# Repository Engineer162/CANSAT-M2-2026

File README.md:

# CANSAT-M2-2026 "Rod From God MK1"

This repository contains all the sources for a highly advanced CANSAT based on an STM32 MCU and featuring a rechargeable lithium polymer battery.

Core hardware fields:

| Component        | Model           | Manufacturer       |
| ---------------- | --------------- | ------------------ |
| STM32 MCU (core) | STM32H7S3L8H6   | STMicroelectronics |

Power system:

| Component          | Model                   | Manufacturer       |
| ------------------ | ----------------------- | ------------------ |
| STM32 MCU (power)  | STM32L031G6U6           | STMicroelectronics |
| USB-C Connector    | 12402012E212A           | Amphenol           |
| Battery Management | BQ25895RTWT             | Texas Instruments  |
| PD Negotiation     | TPS25730DREFR           | Texas Instruments  |
| Battery            | 1260110 (10000mAh LiPo) | TBD                |

Additionally, it features numerous different sensors for logging, as listed below:

| Sensor                | Model          | Manufacturer       |
| --------------------- | -------------- | ------------------ |
| IMU                   | ICM-42688-PC   | Tokmas             |
| Barometer             | BMP581         | BOSCH              |
| Magnetometer          | MMC5983MA      | MEMSIC             |
| Temperature (outside) | TMP121AIDBVR   | Texas Instruments  |
| Temperature (inside)  | TMP121AIDBVR   | Texas Instruments  |
| Ground distance (ToF) | VL53L1CXV0FY/1 | STMicroelectronics |

And debugging/programming is done via a TAG-CONNECT TC2050-IDC "Plug-Of-Nails™" connector.

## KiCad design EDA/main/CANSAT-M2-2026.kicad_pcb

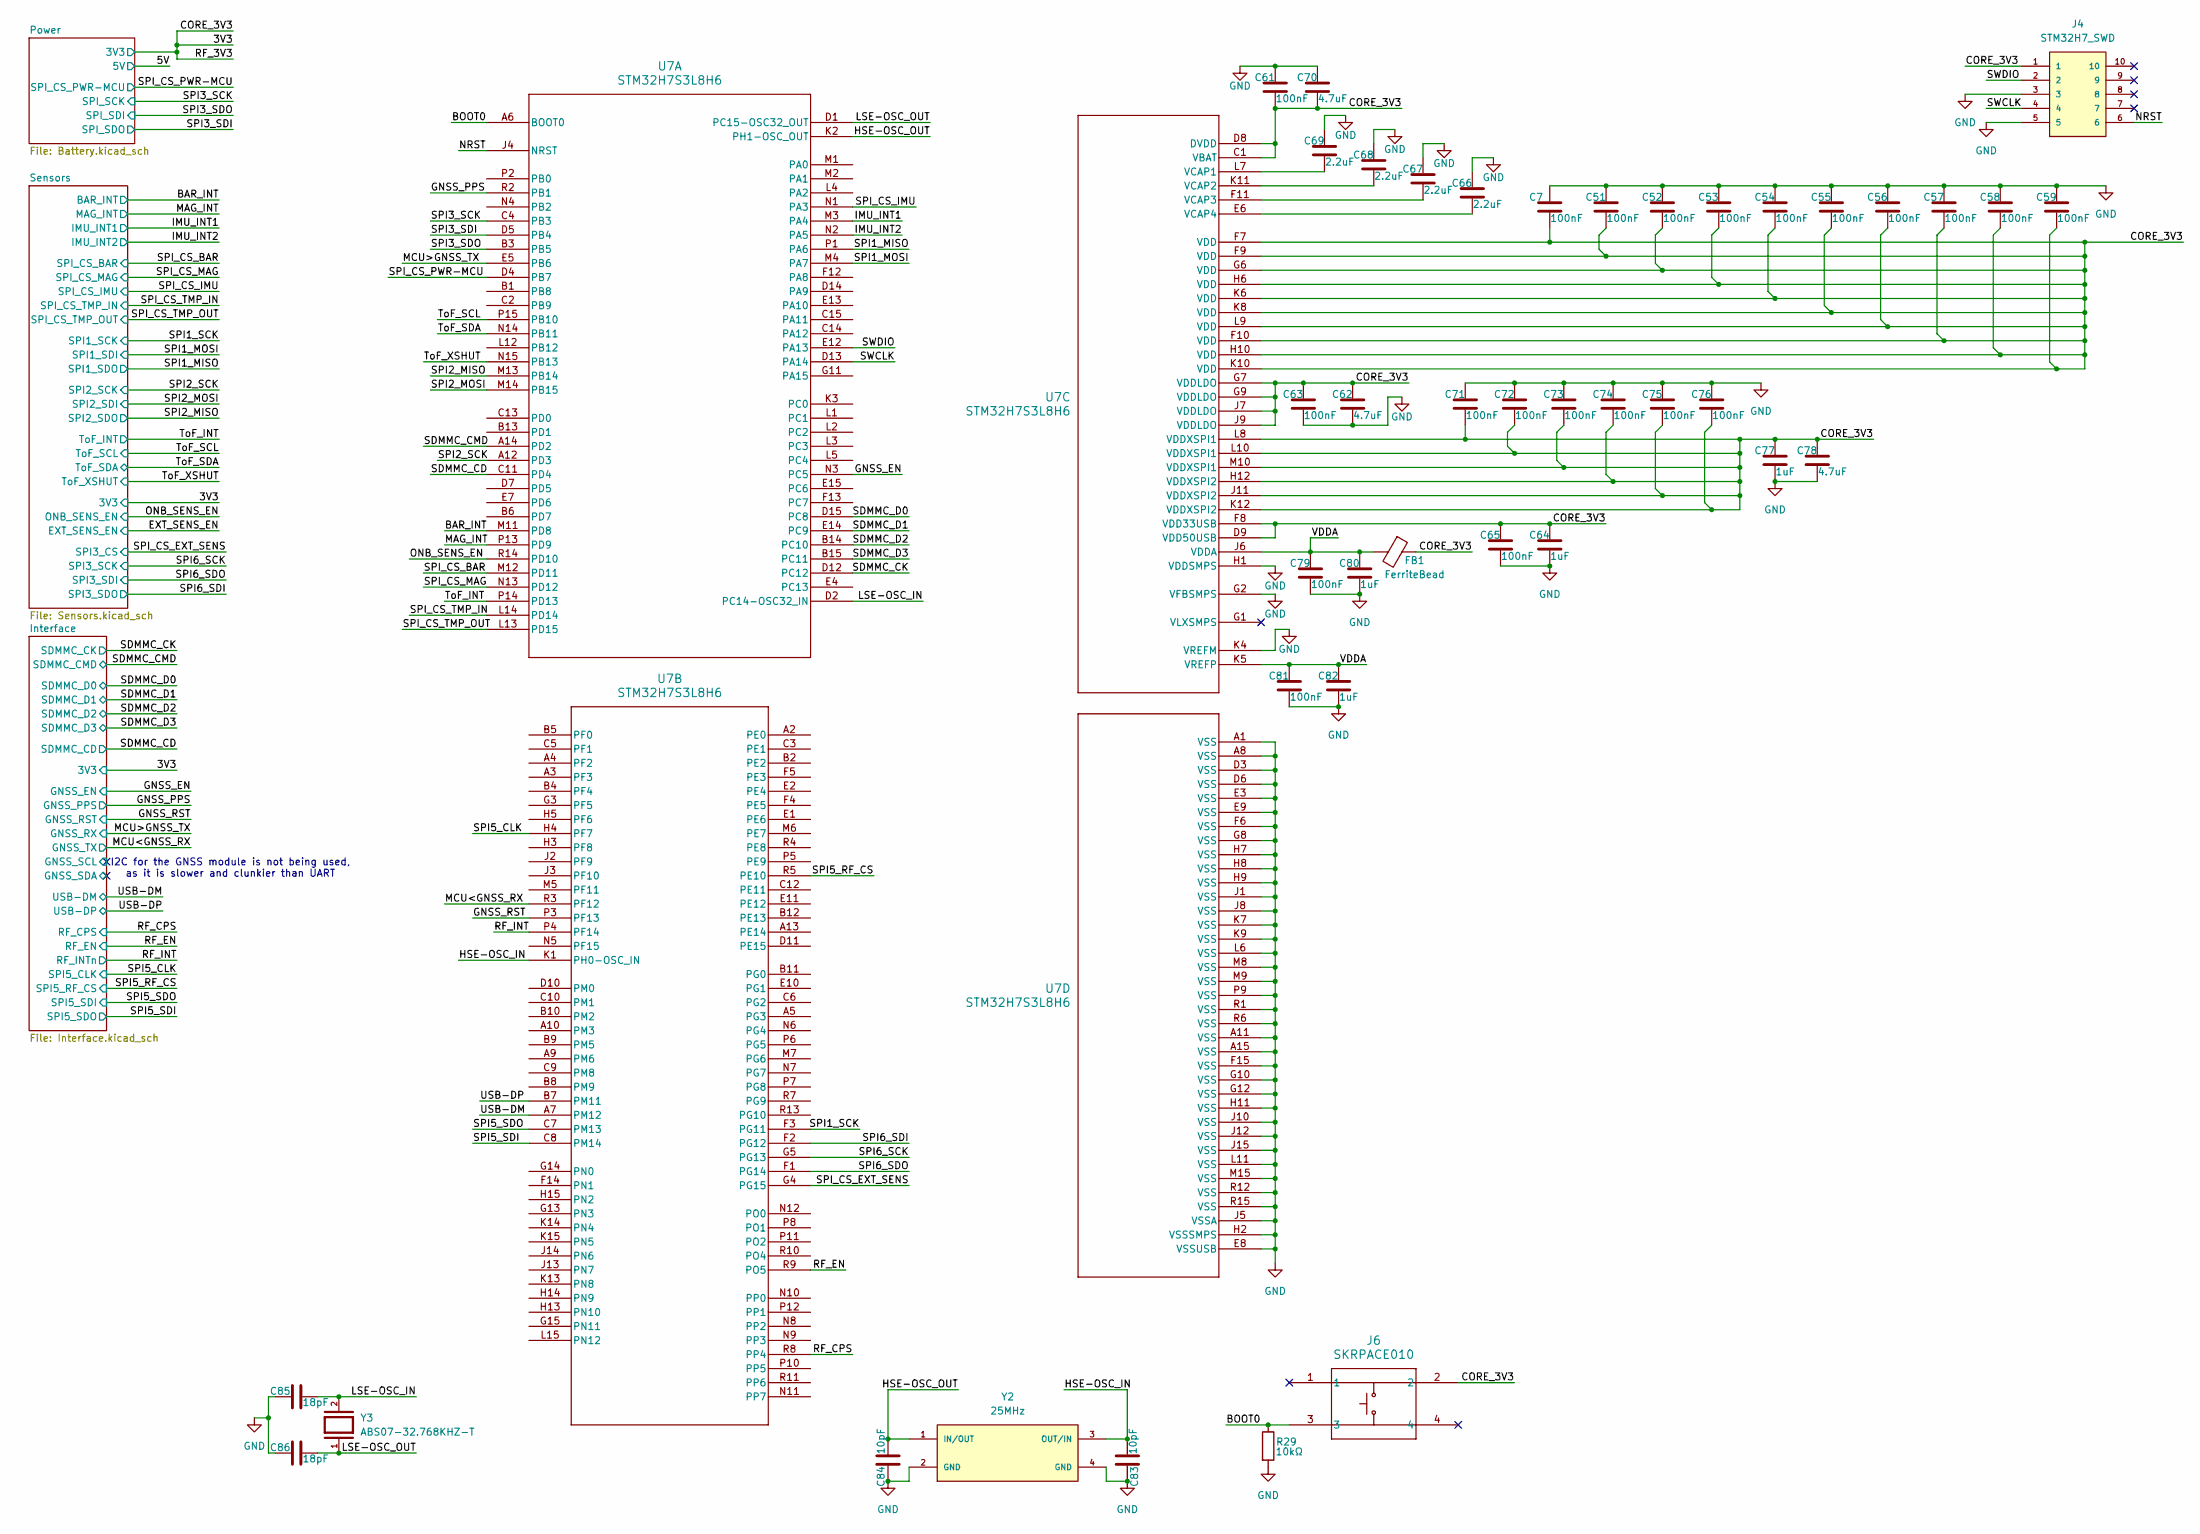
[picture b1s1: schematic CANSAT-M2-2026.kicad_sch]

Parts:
C7, C51, C52, C53, C54, C55, C56, C57, C58, C59, C61, C63, C65, C71, C72, C73, C74, C75, C76, C79, C81: 100nF; C_0402_1005Metric; Manufacturer Part CL05B104KP5NNNC
C62, C70, C78: 4.7uF; C_0603_1608Metric; Manufacturer Part CL10A475KP8NNNC
C64, C77, C80, C82: 1uF; C_0603_1608Metric; Manufacturer Part CL10B105MO8NNWC
C66, C67, C68, C69: 2.2uF; C_0603_1608Metric; Manufacturer Part CL10A225KO8NNNC
C83, C84: 10pF; C_0402_1005Metric; Manufacturer Part CL05C100JB5NNNC
C85, C86: 18pF; C_0402_1005Metric; Manufacturer Part CL05C180JB5NNNC
FB1: FerriteBead; L_0603_1608Metric; Manufacturer Part MMZ1608D121CTAH0
J4: STM32H7_SWD; TAG-CONNECT_TC2050-IDC; PARTREV A; DigiKey_Part_Number TC2050-IDC-ND
J6: SKRPACE010; SW_SKRPACE010_AAL; Manufacturer Part SKRPACE010
R29: 10kΩ; R_0402_1005Metric; Manufacturer Part RC0402FR-0710KL
U7: STM32H7S3L8H6; TFBGA225_13X13_STM; Manufacturer Part STM32H7S3L8H6H
Y2: 25MHz; XTAL_ECS-160-9-37-CKM-TR; PARTREV 2017
Y3: ABS07-32.768KHZ-T; XTAL_ABS07-32.768KHZ-T; PARTREV 08.19.15; DigiKey_Part_Number 535-9542-1-ND

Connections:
/3V3: C7.2, C51.2, C52.2, C53.2, C54.2, C55.2, C56.2, C57.2, C58.2, C59.2, C61.2, C62.1, C63.1, C64.1, C65.1, C70.2, C71.2, C72.2, C73.2, C74.2, C75.2, C76.2, C77.1, C78.1, FB1.1, J4.1, J6.2, U7.C1 (VBAT), U7.D8 (DVDD), U7.D9 (VDD50USB), U7.F7 (VDD), U7.F8 (VDD33USB), U7.F9 (VDD), U7.F10 (VDD), U7.G6 (VDD), U7.G7 (VDDLDO), U7.G9 (VDDLDO), U7.H6 (VDD), U7.H10 (VDD), U7.H12 (VDDXSPI2), U7.J7 (VDDLDO), U7.J9 (VDDLDO), U7.J11 (VDDXSPI2), U7.K6 (VDD), U7.K8 (VDD), U7.K10 (VDD), U7.K12 (VDDXSPI2), U7.L8 (VDDXSPI1), U7.L9 (VDD), U7.L10 (VDDXSPI1), U7.M10 (VDDXSPI1); also elsewhere on the board
/BAR_INT: U7.M11 (PD8); also elsewhere on the board
/BOOT0: J6.3, R29.1, U7.A6 (BOOT0)
/GNSS_EN: U7.N3 (PC5); also elsewhere on the board
/GNSS_PPS: U7.R2 (PB1); also elsewhere on the board
/GNSS_RST: U7.P3 (PF13); also elsewhere on the board
/HSE-OSC_IN: C83.2, U7.K1 (PH0-OSC_IN), Y2.3 (OUT/IN)
/HSE-OSC_OUT: C84.2, U7.K2 (PH1-OSC_OUT), Y2.1 (IN/OUT)
/IMU_INT1: U7.M3 (PA4); also elsewhere on the board
/IMU_INT2: U7.N2 (PA5); also elsewhere on the board
/LSE-OSC_IN: C85.2, U7.D2 (PC14-OSC32_IN), Y3.2
/LSE-OSC_OUT: C86.2, U7.D1 (PC15-OSC32_OUT), Y3.1
/MAG_INT: U7.P13 (PD9); also elsewhere on the board
/MCU<GNSS_RX: U7.R3 (PF12); also elsewhere on the board
/MCU>GNSS_TX: U7.E5 (PB6); also elsewhere on the board
/NRST: J4.6, U7.J4 (NRST)
/ONB_SENS_EN: U7.R14 (PD10); also elsewhere on the board
/RF_CPS: U7.R8 (PP4); also elsewhere on the board
/RF_EN: U7.R9 (PO5); also elsewhere on the board
/RF_INT: U7.P4 (PF14); also elsewhere on the board
/SDMMC_CD: U7.C11 (PD4); also elsewhere on the board
/SDMMC_CK: U7.D12 (PC12); also elsewhere on the board
/SDMMC_CMD: U7.A14 (PD2); also elsewhere on the board
/SDMMC_D0: U7.D15 (PC8); also elsewhere on the board
/SDMMC_D1: U7.E14 (PC9); also elsewhere on the board
/SDMMC_D2: U7.B14 (PC10); also elsewhere on the board
/SDMMC_D3: U7.B15 (PC11); also elsewhere on the board
/SPI1_MISO: U7.P1 (PA6); also elsewhere on the board
/SPI1_MOSI: U7.M4 (PA7); also elsewhere on the board
/SPI1_SCK: U7.F3 (PG11); also elsewhere on the board
/SPI2_MISO: U7.M13 (PB14); also elsewhere on the board
/SPI2_MOSI: U7.M14 (PB15); also elsewhere on the board
/SPI2_SCK: U7.A12 (PD3); also elsewhere on the board
/SPI3_SCK: U7.C4 (PB3); also elsewhere on the board
/SPI3_SDI: U7.D5 (PB4); also elsewhere on the board
/SPI3_SDO: U7.B3 (PB5); also elsewhere on the board
/SPI5_CLK: U7.H4 (PF7); also elsewhere on the board
/SPI5_RF_CS: U7.R5 (PE10); also elsewhere on the board
/SPI5_SDI: U7.C8 (PM14); also elsewhere on the board
/SPI5_SDO: U7.C7 (PM13); also elsewhere on the board
/SPI6_SCK: U7.G5 (PG13); also elsewhere on the board
/SPI6_SDI: U7.F2 (PG12); also elsewhere on the board
/SPI6_SDO: U7.F1 (PG14); also elsewhere on the board
/SPI_CS_BAR: U7.M12 (PD11); also elsewhere on the board
/SPI_CS_EXT_SENS: U7.G4 (PG15); also elsewhere on the board
/SPI_CS_IMU: U7.N1 (PA3); also elsewhere on the board
/SPI_CS_MAG: U7.N13 (PD12); also elsewhere on the board
/SPI_CS_PWR-MCU: U7.D4 (PB7); also elsewhere on the board
/SPI_CS_TMP_IN: U7.L14 (PD14); also elsewhere on the board
/SPI_CS_TMP_OUT: U7.L13 (PD15); also elsewhere on the board
/SWCLK: J4.4, U7.D13 (PA14)
/SWDIO: J4.2, U7.E12 (PA13)
/ToF_INT: U7.P14 (PD13); also elsewhere on the board
/ToF_SCL: U7.P15 (PB10); also elsewhere on the board
/ToF_SDA: U7.N14 (PB11); also elsewhere on the board
/ToF_XSHUT: U7.N15 (PB13); also elsewhere on the board
/USB-DM: U7.A7 (PM12); also elsewhere on the board
/USB-DP: U7.B7 (PM11); also elsewhere on the board
/VDDA: C79.1, C80.1, C81.1, C82.1, FB1.2, U7.J6 (VDDA), U7.K5 (VREFP)
GND: C7.1, C51.1, C52.1, C53.1, C54.1, C55.1, C56.1, C57.1, C58.1, C59.1, C61.1, C62.2, C63.2, C64.2, C65.2, C66.1, C67.1, C68.1, C69.1, C70.1, C71.1, C72.1, C73.1, C74.1, C75.1, C76.1, C77.2, C78.2, C79.2, C80.2, C81.2, C82.2, C83.1, C84.1, C85.1, C86.1, J4.3, J4.5, R29.2, U7.A1 (VSS), U7.A8 (VSS), U7.A11 (VSS), U7.A15 (VSS), U7.D3 (VSS), U7.D6 (VSS), U7.E3 (VSS), U7.E8 (VSSUSB), U7.E9 (VSS), U7.F6 (VSS), U7.F15 (VSS), U7.G2 (VFBSMPS), U7.G8 (VSS), U7.G10 (VSS), U7.G12 (VSS), U7.H1 (VDDSMPS), U7.H2 (VSSSMPS), U7.H7 (VSS), U7.H8 (VSS), U7.H9 (VSS), U7.H11 (VSS), U7.J1 (VSS), U7.J5 (VSSA), U7.J8 (VSS), U7.J10 (VSS), U7.J12 (VSS), U7.J15 (VSS), U7.K4 (VREFM), U7.K7 (VSS), U7.K9 (VSS), U7.L6 (VSS), U7.L11 (VSS), U7.M8 (VSS), U7.M9 (VSS), U7.M15 (VSS), U7.P9 (VSS), U7.R1 (VSS), U7.R6 (VSS), U7.R12 (VSS), U7.R15 (VSS), Y2.2 (GND), Y2.4 (GND); also elsewhere on the board
unnamed: C69.2, U7.L7 (VCAP1)
unnamed: C68.2, U7.K11 (VCAP2)
unnamed: C67.2, U7.F11 (VCAP3)
unnamed: C66.2, U7.E6 (VCAP4)

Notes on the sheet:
I2C for the GNSS module is not being used, as it is slower and clunkier than UART

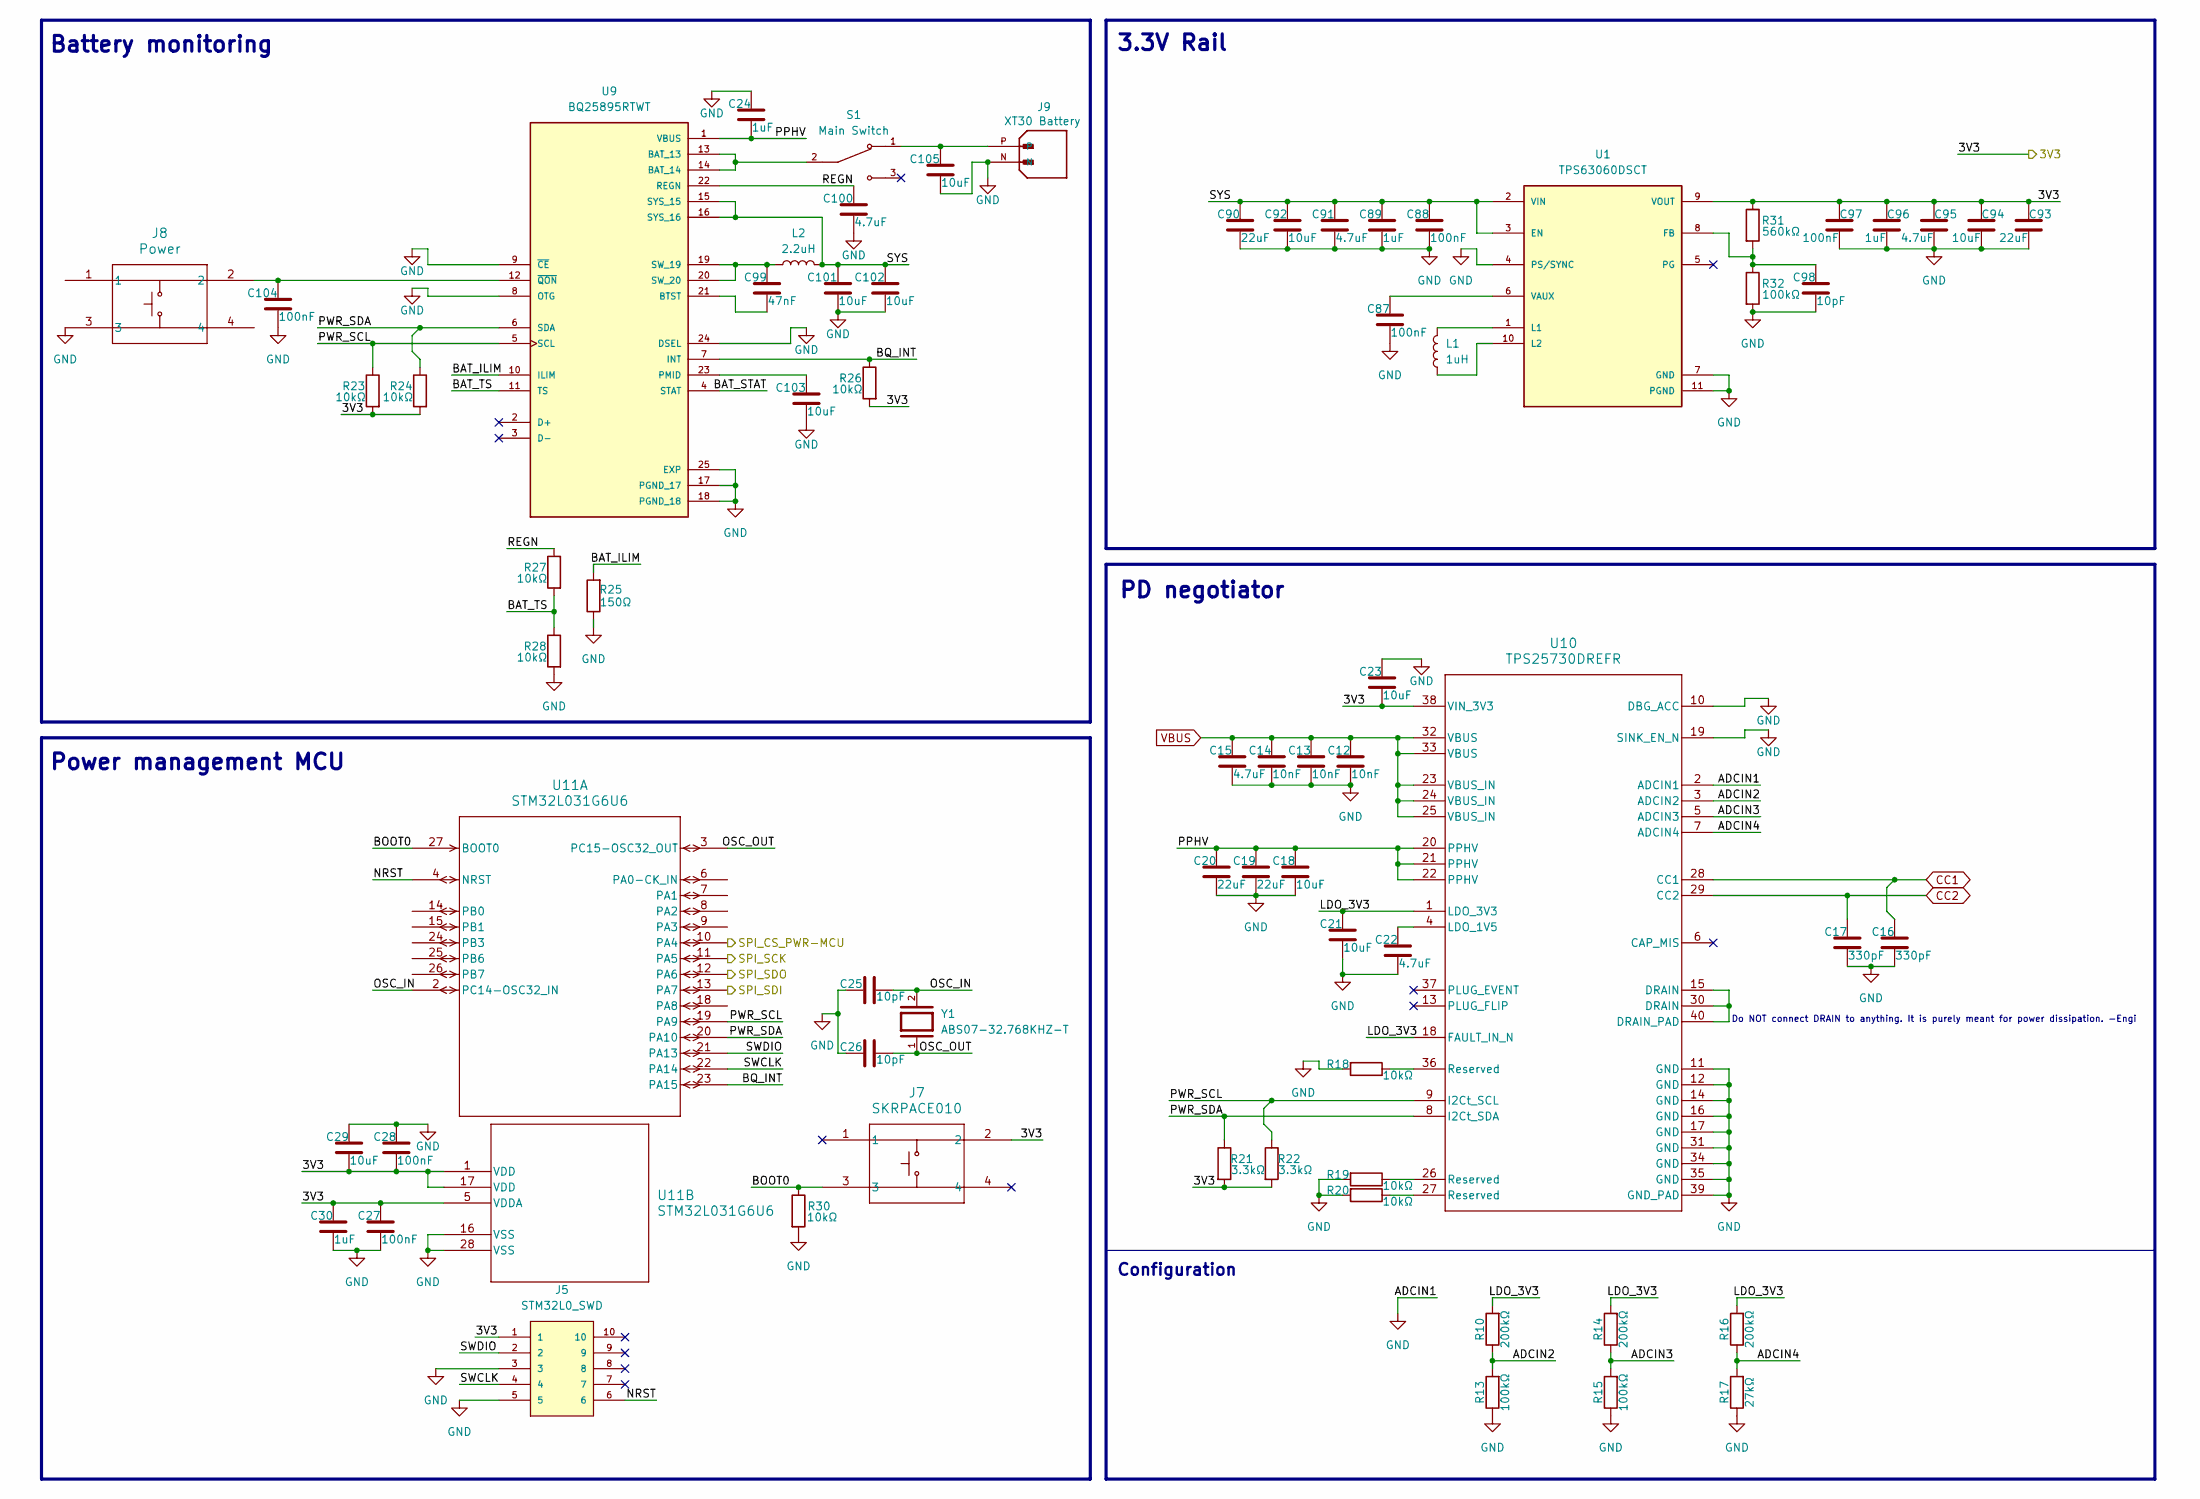
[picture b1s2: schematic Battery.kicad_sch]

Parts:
C12, C13, C14: 10nF; C_0402_1005Metric; Manufacturer Part CL05B103KB5NNNC
C15, C22, C91, C95, C100: 4.7uF; C_0603_1608Metric; Manufacturer Part CL10A475KP8NNNC
C16, C17: 330pF; C_0402_1005Metric; Manufacturer Part CL05C331JB5NNNC
C18, C21, C23, C29, C92, C94, C101, C102, C103, C105: 10uF; C_0603_1608Metric; Manufacturer Part CL10X106MO8NRNC
C19, C20, C90, C93: 22uF; C_0603_1608Metric; Manufacturer Part CL10A226MP8NUNE
C24, C30, C89, C96: 1uF; C_0603_1608Metric; Manufacturer Part CL10B105MO8NNWC
C25, C26, C98: 10pF; C_0402_1005Metric; Manufacturer Part CL05C100JB5NNNC
C27, C28, C87, C88, C97, C104: 100nF; C_0402_1005Metric; Manufacturer Part CL05B104KP5NNNC
C99: 47nF; C_0402_1005Metric; Manufacturer Part CL05B473KB5VPNC
J5: STM32L0_SWD; TAG-CONNECT_TC2050-IDC; PARTREV A; DigiKey_Part_Number TC2050-IDC-ND
J7: SKRPACE010; SW_SKRPACE010_AAL; Manufacturer Part SKRPACE010
J8: Power; SW_SKRPACE010_AAL; Manufacturer Part SKRPACE010
J9: XT30 Battery; AMASS_XT30PW-M; PARTREV 1.2
L1: 1uH; L_1008_2520Metric; Manufacturer Part 74438324010
L2: 2.2uH; L_Wuerth_MAPI-4020; Manufacturer Part 74438356022
R10, R14, R16: 200kΩ; R_0603_1608Metric; Manufacturer Part RC0603JR-07200KL
R13, R15: 100kΩ; R_0603_1608Metric; Manufacturer Part RC0603FR-07100KL
R17: 27kΩ; R_0603_1608Metric; Manufacturer Part RC0603FR-1027KL
R18, R19, R20, R23, R24, R26, R27, R28, R30: 10kΩ; R_0402_1005Metric; Manufacturer Part RC0402FR-0710KL
R21, R22: 3.3kΩ; R_0402_1005Metric; Manufacturer Part RC0402FR-073K3L
R25: 150Ω; R_0603_1608Metric; Manufacturer Part RC0603FR-07150RL
R31: 560kΩ; R_0402_1005Metric; Manufacturer Part RC0402FR-13560KL
R32: 100kΩ; R_0402_1005Metric; Manufacturer Part RC0402FR-07100KL
S1: Main Switch; SW_500SSP1S1M6QEA; PARTREV D
U1: TPS63060DSCT; CONV_TPS63060DSCT; PARTREV B
U9: BQ25895RTWT; QFN50P400X400X80-25N; PARTREV B
U10: TPS25730DREFR; REF0038A-MFG; Manufacturer Part TPS25730DREFR
U11: STM32L031G6U6; UFQFPN28-4x4mm; Manufacturer Part STM32L031G6U6
Y1: ABS07-32.768KHZ-T; XTAL_ABS07-32.768KHZ-T; PARTREV 08.19.15; DigiKey_Part_Number 535-9542-1-ND

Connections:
/3V3: C23.2, C27.1, C28.2, C29.2, C30.1, C93.1, C94.1, C95.1, C96.1, C97.1, J5.1, J7.2, R21.2, R22.2, R23.2, R24.2, R26.2, R31.1, U1.9 (VOUT), U10.38 (VIN_3V3), U11.1 (VDD), U11.5 (VDDA), U11.17 (VDD); also elsewhere on the board
/Power/ADCIN2: R10.1, R13.2, U10.3 (ADCIN2)
/Power/ADCIN3: R14.1, R15.2, U10.5 (ADCIN3)
/Power/ADCIN4: R16.1, R17.2, U10.7 (ADCIN4)
/Power/BAT_ILIM: R25.2, U9.10 (ILIM)
/Power/BAT_STAT: U9.4 (STAT)
/Power/BAT_TS: R27.2, R28.1, U9.11 (TS)
/Power/BOOT0: J7.3, R30.1, U11.27 (BOOT0)
/Power/BQ_INT: R26.1, U9.7 (INT), U11.23 (PA15)
/Power/LDO_3V3: C21.1, R10.2, R14.2, R16.2, U10.1 (LDO_3V3), U10.18 (FAULT_IN_N)
/Power/NRST: J5.6, U11.4 (NRST)
/Power/OSC_IN: C25.2, U11.2 (PC14-OSC32_IN), Y1.2
/Power/OSC_OUT: C26.2, U11.3 (PC15-OSC32_OUT), Y1.1
/Power/PPHV: C18.1, C19.1, C20.1, C24.2, U9.1 (VBUS), U10.20 (PPHV), U10.21 (PPHV), U10.22 (PPHV)
/Power/PWR_SCL: R22.1, R23.1, U9.5 (SCL), U10.9 (I2Ct_SCL), U11.19 (PA9)
/Power/PWR_SDA: R21.1, R24.1, U9.6 (SDA), U10.8 (I2Ct_SDA), U11.20 (PA10)
/Power/REGN: C100.1, R27.1, U9.22 (REGN)
/Power/SWCLK: J5.4, U11.22 (PA14)
/Power/SWDIO: J5.2, U11.21 (PA13)
/Power/SYS: C88.1, C89.1, C90.1, C91.1, C92.1, C101.1, C102.1, L2.2, U1.2 (VIN), U1.3 (EN), U9.15 (SYS_15), U9.16 (SYS_16)
/SPI3_SCK: U11.11 (PA5); also elsewhere on the board
/SPI3_SDI: U11.12 (PA6); also elsewhere on the board
/SPI3_SDO: U11.13 (PA7); also elsewhere on the board
/SPI_CS_PWR-MCU: U11.10 (PA4); also elsewhere on the board
CC1: C16.1, U10.28 (CC1); also elsewhere on the board
CC2: C17.1, U10.29 (CC2); also elsewhere on the board
GND: C12.2, C13.2, C14.2, C15.2, C16.2, C17.2, C18.2, C19.2, C20.2, C21.2, C22.2, C23.1, C24.1, C25.1, C26.1, C27.2, C28.1, C29.1, C30.2, C87.2, C88.2, C89.2, C90.2, C91.2, C92.2, C93.2, C94.2, C95.2, C96.2, C97.2, C98.2, C100.2, C101.2, C102.2, C103.2, C104.2, C105.2, J5.3, J5.5, J8.3, J9.N, R13.1, R15.1, R17.1, R18.2, R19.2, R20.2, R25.1, R28.2, R30.2, R32.2, U1.4 (PS/SYNC), U1.7 (GND), U1.11 (PGND), U9.8 (OTG), U9.9 (~CE), U9.17 (PGND_17), U9.18 (PGND_18), U9.24 (DSEL), U9.25 (EXP), U10.2 (ADCIN1), U10.10 (DBG_ACC), U10.11 (GND), U10.12 (GND), U10.14 (GND), U10.16 (GND), U10.17 (GND), U10.19 (SINK_EN_N), U10.31 (GND), U10.34 (GND), U10.35 (GND), U10.39 (GND_PAD), U11.16 (VSS), U11.28 (VSS); also elsewhere on the board
unnamed: C105.1, J9.P, S1.1
unnamed: R18.1, U10.36 (Reserved)
unnamed: R19.1, U10.26 (Reserved)
unnamed: R20.1, U10.27 (Reserved)
unnamed: C98.1, R31.2, R32.1, U1.8 (FB)
unnamed: L1.2, U1.1 (L1)
unnamed: L1.1, U1.10 (L2)
unnamed: C87.1, U1.6 (VAUX)
unnamed: S1.2, U9.13 (BAT_13), U9.14 (BAT_14)
unnamed: C99.2, U9.21 (BTST)
unnamed: C103.1, U9.23 (PMID)
unnamed: C99.1, L2.1, U9.19 (SW_19), U9.20 (SW_20)
unnamed: C104.1, J8.2, U9.12 (~QON)
unnamed: U10.15 (DRAIN), U10.30 (DRAIN), U10.40 (DRAIN_PAD)
unnamed: C22.1, U10.4 (LDO_1V5)
VBUS: C12.1, C13.1, C14.1, C15.1, U10.23 (VBUS_IN), U10.24 (VBUS_IN), U10.25 (VBUS_IN), U10.32 (VBUS), U10.33 (VBUS); also elsewhere on the board

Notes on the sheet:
Power management MCU
Battery monitoring
3.3V Rail
Configuration
Do NOT connect DRAIN to anything. It is purely meant for power dissipation. -Engi
PD negotiator

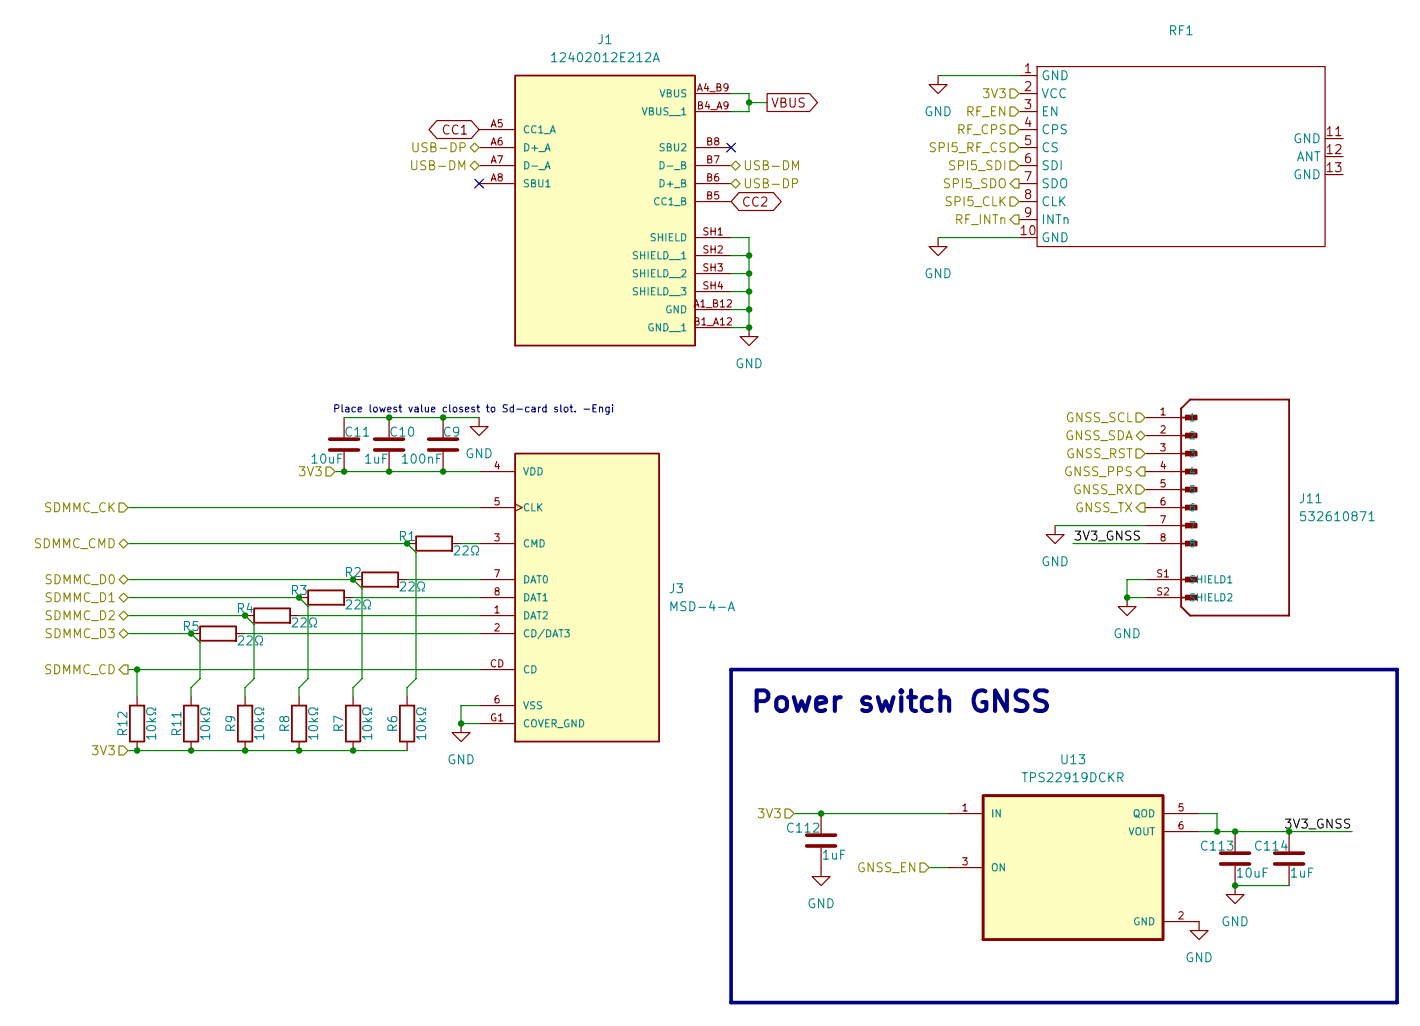
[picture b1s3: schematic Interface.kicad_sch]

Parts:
C9: 100nF; C_0402_1005Metric; Manufacturer Part CL05B104KP5NNNC
C10, C112, C114: 1uF; C_0603_1608Metric; Manufacturer Part CL10B105MO8NNWC
C11, C113: 10uF; C_0603_1608Metric; Manufacturer Part CL10X106MO8NRNC
J1: 12402012E212A; AMPHENOL_USB-C_12402012E212A; PARTREV 4
J3: MSD-4-A; CUI_MSD-4-A; PARTREV 1.0; DigiKey_Part_Number 2223-MSD-4-ACT-ND
J11: 532610871; MOLEX_532610871; PARTREV J
R1, R2, R3, R4, R5: 22Ω; R_0402_1005Metric; Manufacturer Part RC0402FR-0722RL
R6, R7, R8, R9, R11, R12: 10kΩ; R_0402_1005Metric; Manufacturer Part RC0402FR-0710KL
RF1: SI4463-MODULE
U13: TPS22919DCKR; SOT65P210X110-6N; Manufacturer Part TPS22919DCKR

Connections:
/3V3: C9.2, C10.2, C11.2, C112.1, J3.4 (VDD), R6.1, R7.1, R8.1, R9.1, R11.1, R12.1, RF1.2 (VCC), U13.1 (IN); also elsewhere on the board
/GNSS_EN: U13.3 (ON); also elsewhere on the board
/GNSS_PPS: J11.4; also elsewhere on the board
/GNSS_RST: J11.3; also elsewhere on the board
/Interface/3V3_GNSS: C113.1, C114.1, J11.8, U13.5 (QOD), U13.6 (VOUT)
/Interface/GNSS_SCL: J11.1
/Interface/GNSS_SDA: J11.2
/MCU<GNSS_RX: J11.6; also elsewhere on the board
/MCU>GNSS_TX: J11.5; also elsewhere on the board
/RF_CPS: RF1.4 (CPS); also elsewhere on the board
/RF_EN: RF1.3 (EN); also elsewhere on the board
/RF_INT: RF1.9 (INTn); also elsewhere on the board
/SDMMC_CD: J3.CD, R12.2; also elsewhere on the board
/SDMMC_CK: J3.5 (CLK); also elsewhere on the board
/SDMMC_CMD: R1.1, R6.2; also elsewhere on the board
/SDMMC_D0: R2.1, R7.2; also elsewhere on the board
/SDMMC_D1: R3.1, R8.2; also elsewhere on the board
/SDMMC_D2: R4.1, R9.2; also elsewhere on the board
/SDMMC_D3: R5.1, R11.2; also elsewhere on the board
/SPI5_CLK: RF1.8 (CLK); also elsewhere on the board
/SPI5_RF_CS: RF1.5 (CS); also elsewhere on the board
/SPI5_SDI: RF1.7 (SDO); also elsewhere on the board
/SPI5_SDO: RF1.6 (SDI); also elsewhere on the board
/USB-DM: J1.A7 (D-_A), J1.B7 (D-_B); also elsewhere on the board
/USB-DP: J1.A6 (D+_A), J1.B6 (D+_B); also elsewhere on the board
CC1: J1.A5 (CC1_A); also elsewhere on the board
CC2: J1.B5 (CC1_B); also elsewhere on the board
GND: C9.1, C10.1, C11.1, C112.2, C113.2, C114.2, J1.A1_B12 (GND), J1.B1_A12 (GND__1), J1.SH1 (SHIELD), J1.SH2 (SHIELD__1), J1.SH3 (SHIELD__2), J1.SH4 (SHIELD__3), J3.6 (VSS), J3.G1 (COVER_GND), J3.G2 (COVER_GND), J3.G3 (COVER_GND), J3.G4 (COVER_GND), J11.7, J11.S1 (SHIELD1), J11.S2 (SHIELD2), RF1.1 (GND), RF1.10 (GND), U13.2 (GND); also elsewhere on the board
unnamed: J3.2 (CD/DAT3), R5.2
unnamed: J3.3 (CMD), R1.2
unnamed: J3.7 (DAT0), R2.2
unnamed: J3.8 (DAT1), R3.2
unnamed: J3.1 (DAT2), R4.2
VBUS: J1.A4_B9 (VBUS), J1.B4_A9 (VBUS__1); also elsewhere on the board

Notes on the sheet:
Place lowest value closest to Sd-card slot. -Engi
Power switch GNSS

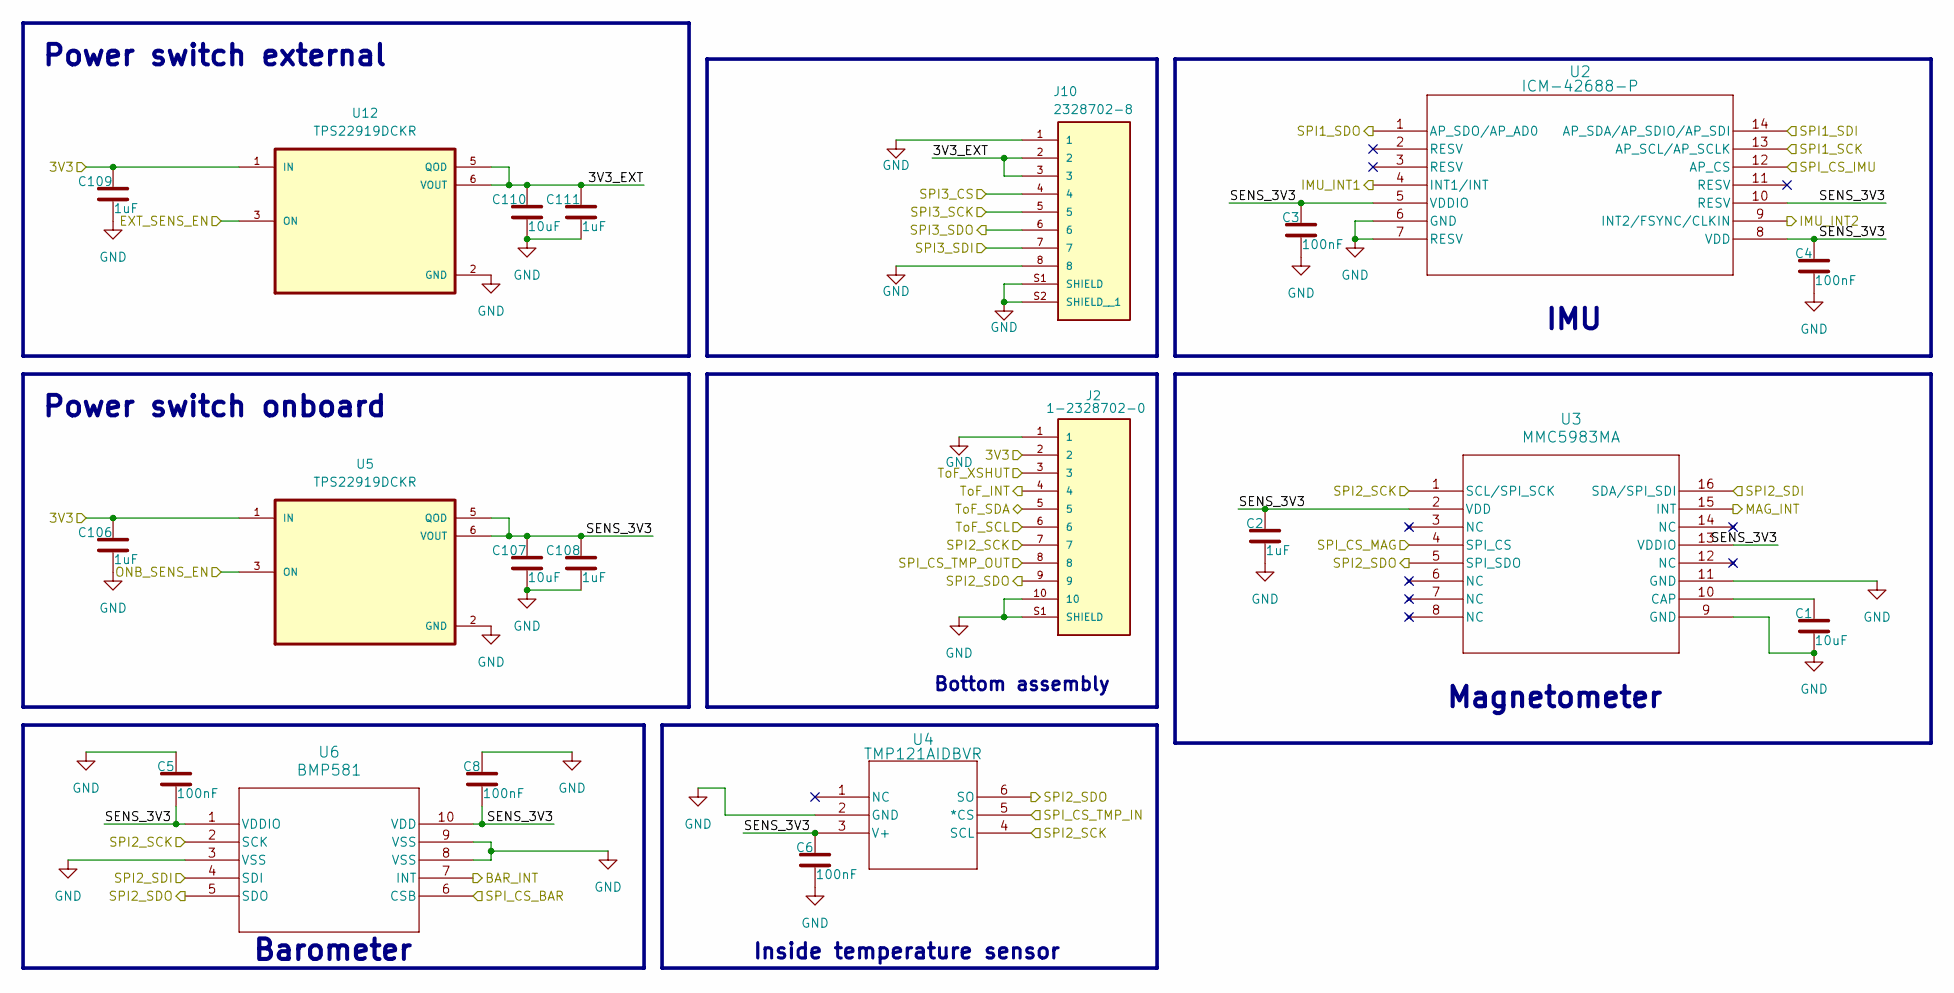
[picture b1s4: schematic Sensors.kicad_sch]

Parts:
C1, C107, C110: 10uF; C_0603_1608Metric; Manufacturer Part CL10X106MO8NRNC
C2, C106, C108, C109, C111: 1uF; C_0603_1608Metric; Manufacturer Part CL10B105MO8NNWC
C3, C4, C5, C6, C8: 100nF; C_0402_1005Metric; Manufacturer Part CL05B104KP5NNNC
J2: 1-2328702-0; TE_1-2328702-0; PARTREV 5; DigiKey_Part_Number A141390CT-ND
J10: 2328702-8; TE_2328702-8; PARTREV 5
U2: ICM-42688-P; LGA14_2P5X3X0P91_TDK; Manufacturer Part ICM-42688-P
U3: MMC5983MA; MMC5983MA_MEM; Manufacturer Part MMC5983MA
U4: TMP121AIDBVR; DBV6; Manufacturer Part TMP121AIDBVR
U5, U12: TPS22919DCKR; SOT65P210X110-6N; Manufacturer Part TPS22919DCKR
U6: BMP581; QFN10_BMP581_BOS; Manufacturer Part BMP581

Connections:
/3V3: C106.1, C109.1, J2.2, U5.1 (IN), U12.1 (IN); also elsewhere on the board
/BAR_INT: U6.7 (INT); also elsewhere on the board
/EXT_SENS_EN: U12.3 (ON)
/IMU_INT1: U2.4 (INT1/INT); also elsewhere on the board
/IMU_INT2: U2.9 (INT2/FSYNC/CLKIN); also elsewhere on the board
/MAG_INT: U3.15 (INT); also elsewhere on the board
/ONB_SENS_EN: U5.3 (ON); also elsewhere on the board
/SPI1_MISO: U2.1 (AP_SDO/AP_AD0); also elsewhere on the board
/SPI1_MOSI: U2.14 (AP_SDA/AP_SDIO/AP_SDI); also elsewhere on the board
/SPI1_SCK: U2.13 (AP_SCL/AP_SCLK); also elsewhere on the board
/SPI2_MISO: J2.9, U3.5 (SPI_SDO), U4.6 (SO), U6.5 (SDO); also elsewhere on the board
/SPI2_MOSI: U3.16 (SDA/SPI_SDI), U6.4 (SDI); also elsewhere on the board
/SPI2_SCK: J2.7, U3.1 (SCL/SPI_SCK), U4.4 (SCL), U6.2 (SCK); also elsewhere on the board
/SPI6_SCK: J10.5; also elsewhere on the board
/SPI6_SDI: J10.6; also elsewhere on the board
/SPI6_SDO: J10.7; also elsewhere on the board
/SPI_CS_BAR: U6.6 (CSB); also elsewhere on the board
/SPI_CS_EXT_SENS: J10.4; also elsewhere on the board
/SPI_CS_IMU: U2.12 (AP_CS); also elsewhere on the board
/SPI_CS_MAG: U3.4 (SPI_CS); also elsewhere on the board
/SPI_CS_TMP_IN: U4.5 (*CS); also elsewhere on the board
/SPI_CS_TMP_OUT: J2.8; also elsewhere on the board
/Sensors/3V3_EXT: C110.1, C111.1, J10.2, J10.3, U12.5 (QOD), U12.6 (VOUT)
/Sensors/SENS_3V3: C2.1, C3.1, C4.1, C5.2, C6.1, C8.2, C107.1, C108.1, U2.5 (VDDIO), U2.8 (VDD), U2.10 (RESV), U3.2 (VDD), U3.13 (VDDIO), U4.3 (V+), U5.5 (QOD), U5.6 (VOUT), U6.1 (VDDIO), U6.10 (VDD)
/ToF_INT: J2.4; also elsewhere on the board
/ToF_SCL: J2.6; also elsewhere on the board
/ToF_SDA: J2.5; also elsewhere on the board
/ToF_XSHUT: J2.3; also elsewhere on the board
GND: C1.2, C2.2, C3.2, C4.2, C5.1, C6.2, C8.1, C106.2, C107.2, C108.2, C109.2, C110.2, C111.2, J2.1, J2.10, J2.S1 (SHIELD), J2.S2 (SHIELD), J10.1, J10.8, J10.S1 (SHIELD), J10.S2 (SHIELD__1), U2.6 (GND), U2.7 (RESV), U3.9 (GND), U3.11 (GND), U4.2 (GND), U5.2 (GND), U6.3 (VSS), U6.8 (VSS), U6.9 (VSS), U12.2 (GND); also elsewhere on the board
unnamed: C1.1, U3.10 (CAP)

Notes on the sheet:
Power switch onboard
Barometer
Magnetometer
Bottom assembly
Inside temperature sensor
IMU
Power switch external

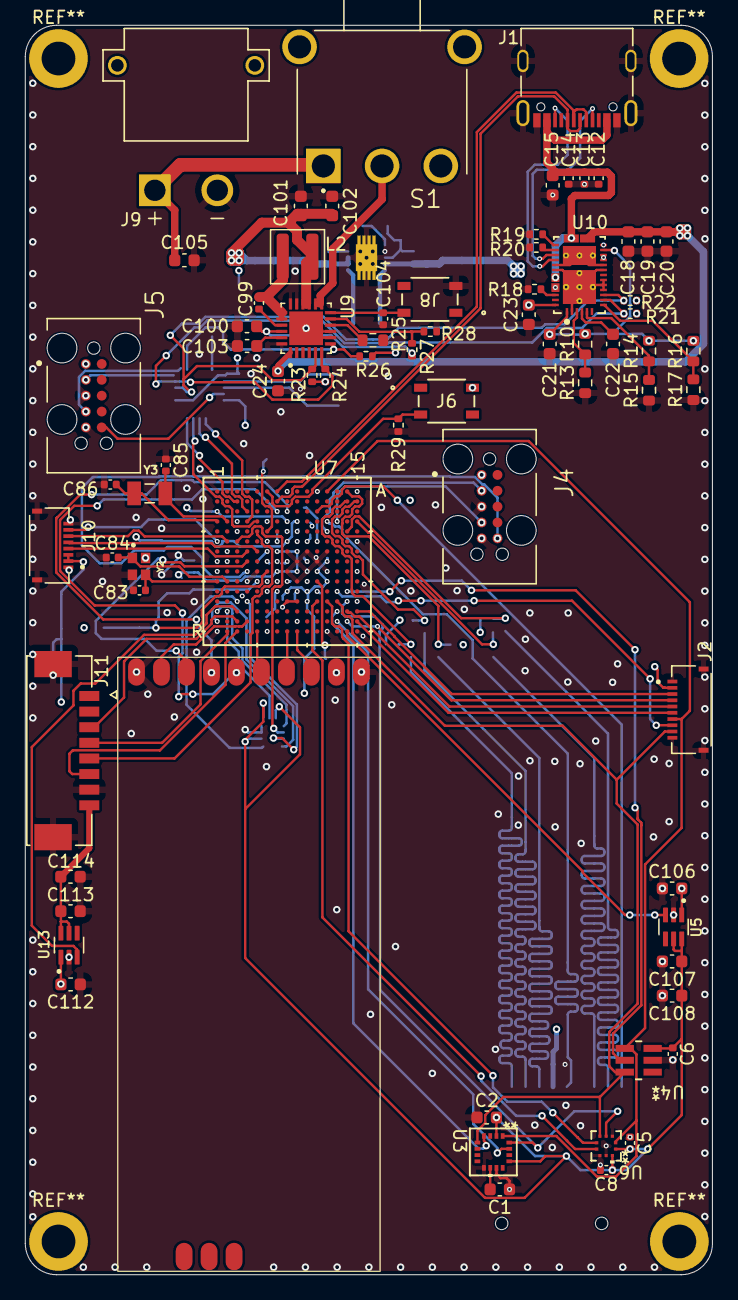
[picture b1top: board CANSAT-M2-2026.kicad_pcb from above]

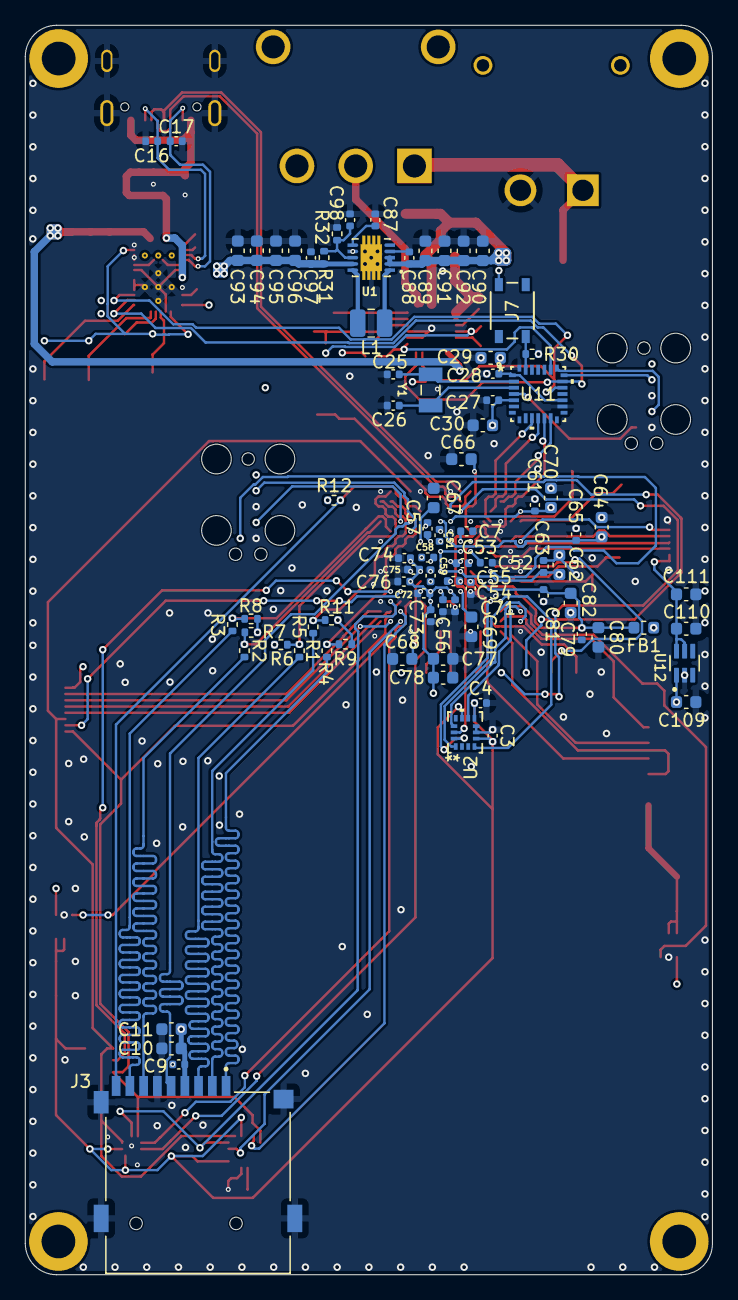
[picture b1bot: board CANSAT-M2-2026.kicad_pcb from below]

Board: 4 copper layers, 55.0 x 100.0 mm, 156 parts (83 on the bottom side), 109 nets.
